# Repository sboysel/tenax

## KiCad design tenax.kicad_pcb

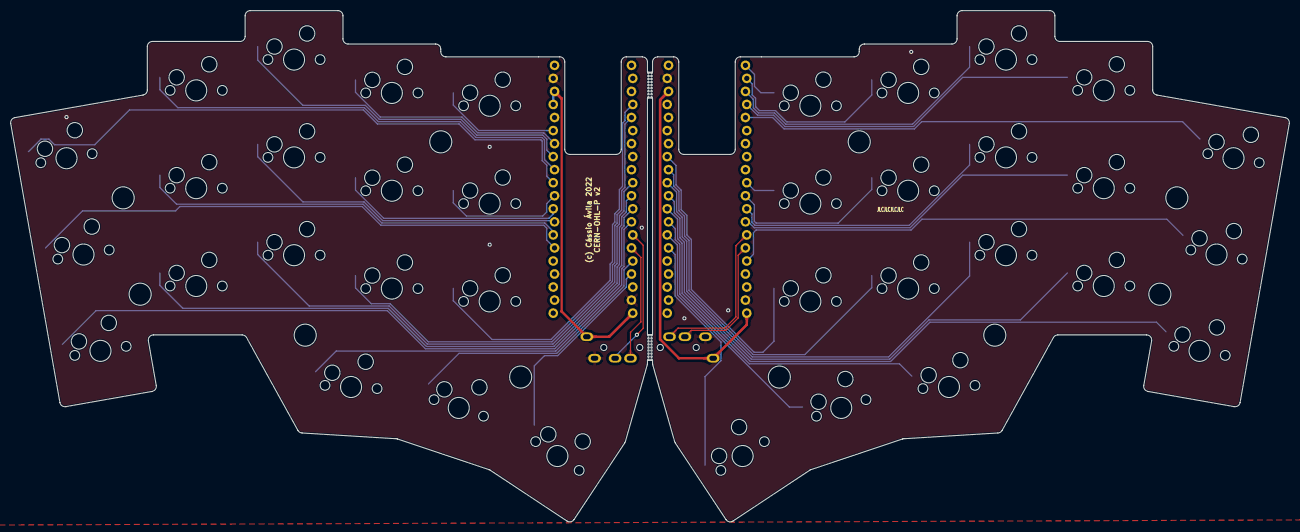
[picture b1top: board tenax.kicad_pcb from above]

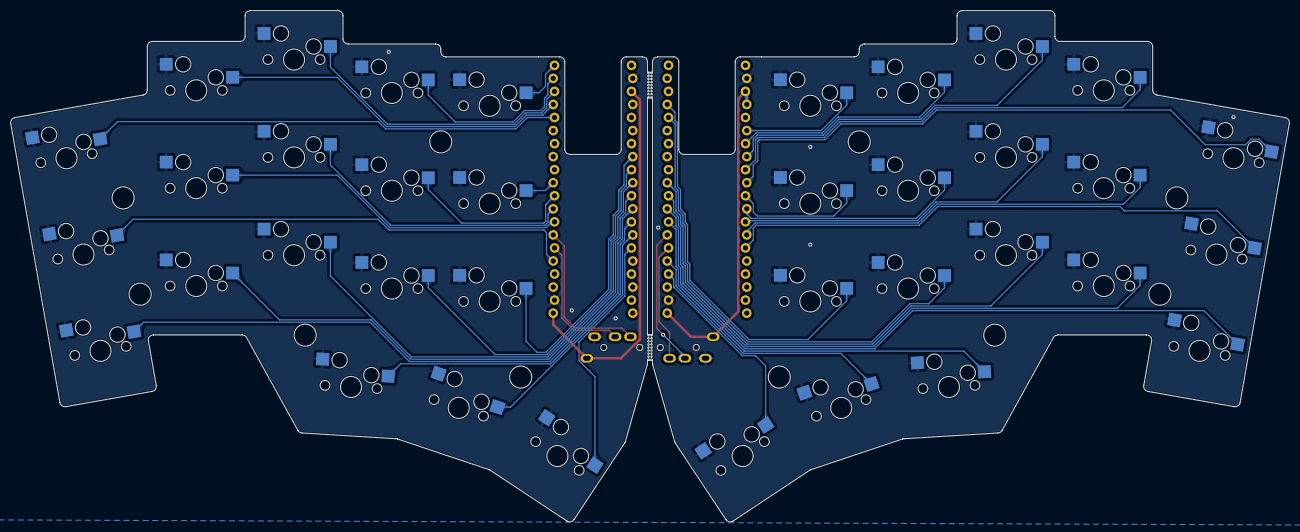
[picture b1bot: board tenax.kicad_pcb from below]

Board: 2 copper layers, 249.0 x 99.5 mm, 54 parts (2 on the bottom side), 42 nets.

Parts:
H1, H2, H13, H14: Breakaway Tabs; Breakaway_Tabs
H3, H4, H5, H6, H7, H8, H9, H10, H11, H12: MountingHole; M2_HOLE_v2
J1, J2: AudioJack4; MJ-4PP-9_1side
SW1, SW2, SW3, SW4, SW5, SW6, SW7, SW8, SW9, SW10, SW11, SW12, SW13, SW14, SW15, SW16, SW17, SW18, SW19, SW20, SW21, SW22, SW23, SW24, SW25, SW26, SW27, SW28, SW29, SW30, SW31, SW32, SW33, SW34, SW35, SW36: SW_SPST; CherryMX_Hotswap
U1, U2: YAAJ_WeAct_BlackPill_Part_Like; BlackPill_STLINK

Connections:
+3V3: J1.S, J2.S, U1.20 (3V3), U1.37 (PB10), U1.38 (3V3), U2.20 (3V3), U2.38 (3V3)
/k0_0: SW1.1 (A), U1.31 (PA5)
/k0_1: SW4.1 (A), U1.32 (PA6)
/k0_2: SW7.1 (A), U1.33 (PA7)
/k0_3: SW11.1 (A), U1.34 (PB0)
/k0_4: SW15.1 (A), U1.35 (PB1)
/k0_5: SW19.1 (A), U2.1 (PB12)
/k0_6: SW23.1 (A), U2.2 (PB13)
/k0_7: SW27.1 (A), U2.3 (PB14)
/k0_8: SW31.1 (A), U2.4 (PB15)
/k0_9: SW34.1 (A), U2.5 (PA8)
/k1_0: SW2.1 (A), U1.26 (PA0)
/k1_1: SW5.1 (A), U1.27 (PA1)
/k1_2: SW8.1 (A), U1.28 (PA2)
/k1_3: SW12.1 (A), U1.29 (PA3)
/k1_4: SW16.1 (A), U1.30 (PA4)
/k1_5: SW20.1 (A), U2.10 (PA15)
/k1_6: SW24.1 (A), U2.11 (PB3)
/k1_7: SW28.1 (A), U2.12 (PB4)
/k1_8: SW32.1 (A), U2.13 (PB5)
/k1_9: SW35.1 (A), U2.16 (PB8)
/k2_0: SW3.1 (A), U1.12 (PB4)
/k2_1: SW6.1 (A), U1.11 (PB3)
/k2_2: SW9.1 (A), U1.10 (PA15)
/k2_3: SW13.1 (A), U1.5 (PA8)
/k2_4: SW17.1 (A), U1.4 (PB15)
/k2_5: SW21.1 (A), U2.33 (PA7)
/k2_6: SW25.1 (A), U2.32 (PA6)
/k2_7: SW29.1 (A), U2.31 (PA5)
/k2_8: SW33.1 (A), U2.30 (PA4)
/k2_9: SW36.1 (A), U2.29 (PA3)
/k3_0: SW10.1 (A), U1.13 (PB5)
/k3_1: SW14.1 (A), U1.16 (PB8)
/k3_2: SW18.1 (A), U1.17 (PB9)
/k3_3: SW22.1 (A), U2.26 (PA0)
/k3_4: SW26.1 (A), U2.27 (PA1)
/k3_5: SW30.1 (A), U2.28 (PA2)
GND: J1.T, J2.T, SW1.2 (B), SW2.2 (B), SW3.2 (B), SW4.2 (B), SW5.2 (B), SW6.2 (B), SW7.2 (B), SW8.2 (B), SW9.2 (B), SW10.2 (B), SW11.2 (B), SW12.2 (B), SW13.2 (B), SW14.2 (B), SW15.2 (B), SW16.2 (B), SW17.2 (B), SW18.2 (B), SW19.2 (B), SW20.2 (B), SW21.2 (B), SW22.2 (B), SW23.2 (B), SW24.2 (B), SW25.2 (B), SW26.2 (B), SW27.2 (B), SW28.2 (B), SW29.2 (B), SW30.2 (B), SW31.2 (B), SW32.2 (B), SW33.2 (B), SW34.2 (B), SW35.2 (B), SW36.2 (B), U1.19 (GND), U1.39 (GND), U2.19 (GND), U2.39 (GND)
RX_l: J1.R2, U1.15 (PB7)
RX_r: J2.R1, U2.15 (PB7)
TX_l: J1.R1, U1.14 (PB6)
TX_r: J2.R2, U2.14 (PB6)

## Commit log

2023-04-21 re-route LHS TX line
2023-04-21 solid ground fill
2023-04-21 teardrops
2023-04-25 ground via for LHS near MCU
2023-04-25 add silkscreen, update gerbers

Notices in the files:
tenax.kicad_pcb:
CERN-OHL-P v2
